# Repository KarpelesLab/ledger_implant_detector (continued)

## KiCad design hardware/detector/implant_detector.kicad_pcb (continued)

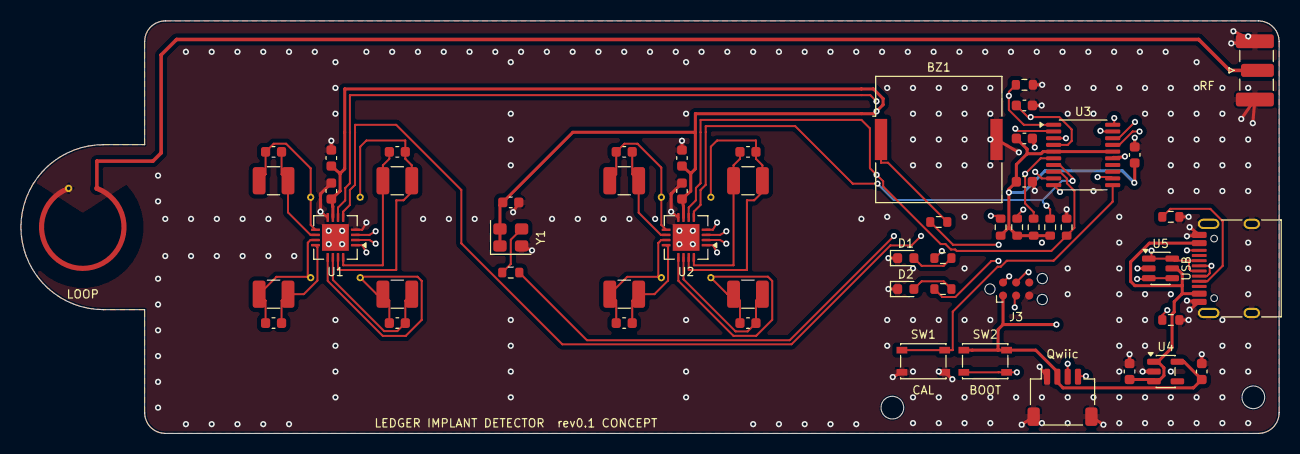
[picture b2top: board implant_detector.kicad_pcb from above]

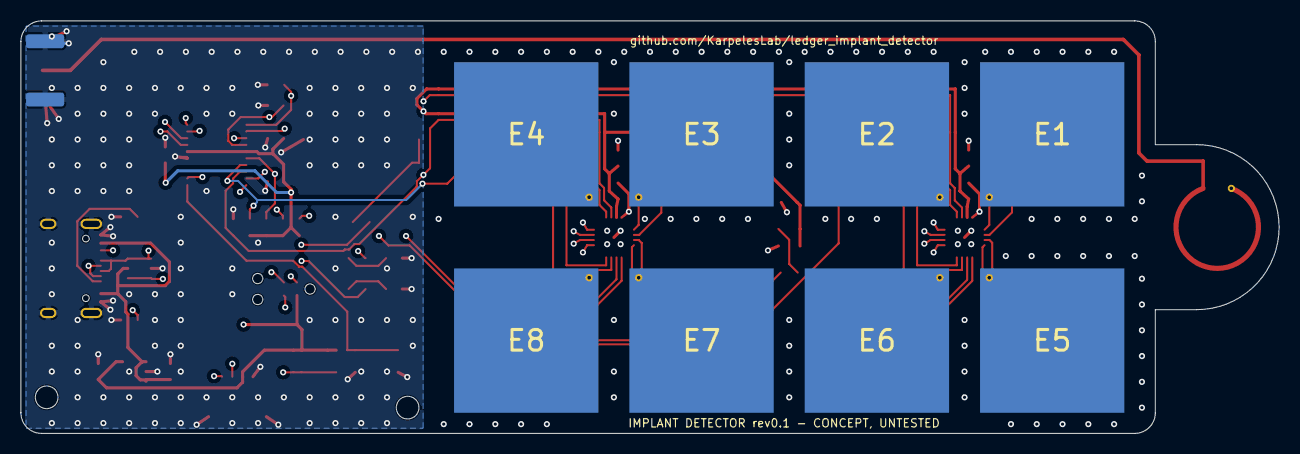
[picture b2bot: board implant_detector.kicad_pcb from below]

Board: 4 copper layers, 122.0 x 40.0 mm, 65 parts (8 on the bottom side), 42 nets.

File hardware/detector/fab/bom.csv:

"Designator","Value","Footprint","MPN","Manufacturer","LCSC","Qty","DNP"
"BZ1","PKLCS1212E4001","Buzzer_Beeper:Buzzer_Murata_PKLCS1212E","PKLCS1212E4001-R1","Murata","","1",""
"C1-C8","33p","Capacitor_SMD:C_0603_1608Metric","GRM1885C1H330FA01D","Murata","","8",""
"C9,C10,C13","4.7u","Capacitor_SMD:C_0603_1608Metric","","","","3",""
"C11,C12,C14,C15,C17,C19","100n","Capacitor_SMD:C_0603_1608Metric","","","","6",""
"C16,C18","1u","Capacitor_SMD:C_0603_1608Metric","","","","2",""
"D1","GREEN","LED_SMD:LED_0603_1608Metric","19-217/GHC-YR1S2/3T","Everlight","","1",""
"D2","RED","LED_SMD:LED_0603_1608Metric","19-217/R6C-AL1M2VY/3T","Everlight","","1",""
"J1","USB-C","Connector_USB:USB_C_Receptacle_HRO_TYPE-C-31-M-12","TYPE-C-31-M-12","Korean Hroparts Elec","C165948","1",""
"J2","Qwiic","Connector_JST:JST_SH_SM04B-SRSS-TB_1x04-1MP_P1.00mm_Horizontal","SM04B-SRSS-TB(LF)(SN)","JST","","1",""
"J4","SMA","Connector_Coaxial:SMA_Samtec_SMA-J-P-H-ST-EM1_EdgeMount","SMA-J-P-H-ST-EM1","Samtec","","1",""
"L1-L8","18u","Inductor_SMD:L_1210_3225Metric","CMH322522-180KL","Bourns","","8",""
"R1,R2","5.1k","Resistor_SMD:R_0603_1608Metric","","","","2",""
"R3,R9,R10","10k","Resistor_SMD:R_0603_1608Metric","","","","3",""
"R4,R5","1k","Resistor_SMD:R_0603_1608Metric","","","","2",""
"R6","100","Resistor_SMD:R_0603_1608Metric","","","","1",""
"R7,R8","4.7k","Resistor_SMD:R_0603_1608Metric","","","","2",""
"R11","100k","Resistor_SMD:R_0603_1608Metric","","","","1",""
"R12","33","Resistor_SMD:R_0603_1608Metric","","","","1",""
"SW1","CAL","Button_Switch_SMD:SW_SPST_PTS810","PTS810 SJM 250 SMTR LFS","C&K","","1",""
"SW2","BOOT","Button_Switch_SMD:SW_SPST_PTS810","PTS810 SJM 250 SMTR LFS","C&K","","1",""
"U1,U2","FDC2214","Package_DFN_QFN:WQFN-16-1EP_4x4mm_P0.5mm_EP2.6x2.6mm","FDC2214RGHR","Texas Instruments","","2",""
"U3","STM32F042F6P6","Package_SO:TSSOP-20_4.4x6.5mm_P0.65mm","STM32F042F6P6","STMicroelectronics","","1",""
"U4","AP2112K-3.3","Package_TO_SOT_SMD:SOT-23-5","AP2112K-3.3TRG1","Diodes Inc","","1",""
"U5","USBLC6-2SC6","Package_TO_SOT_SMD:SOT-23-6","USBLC6-2SC6","STMicroelectronics","","1",""
"Y1","40MHz","Oscillator:Oscillator_SMD_Abracon_ASE-4Pin_3.2x2.5mm","ASE-40.000MHZ-LC-T","Abracon","","1",""

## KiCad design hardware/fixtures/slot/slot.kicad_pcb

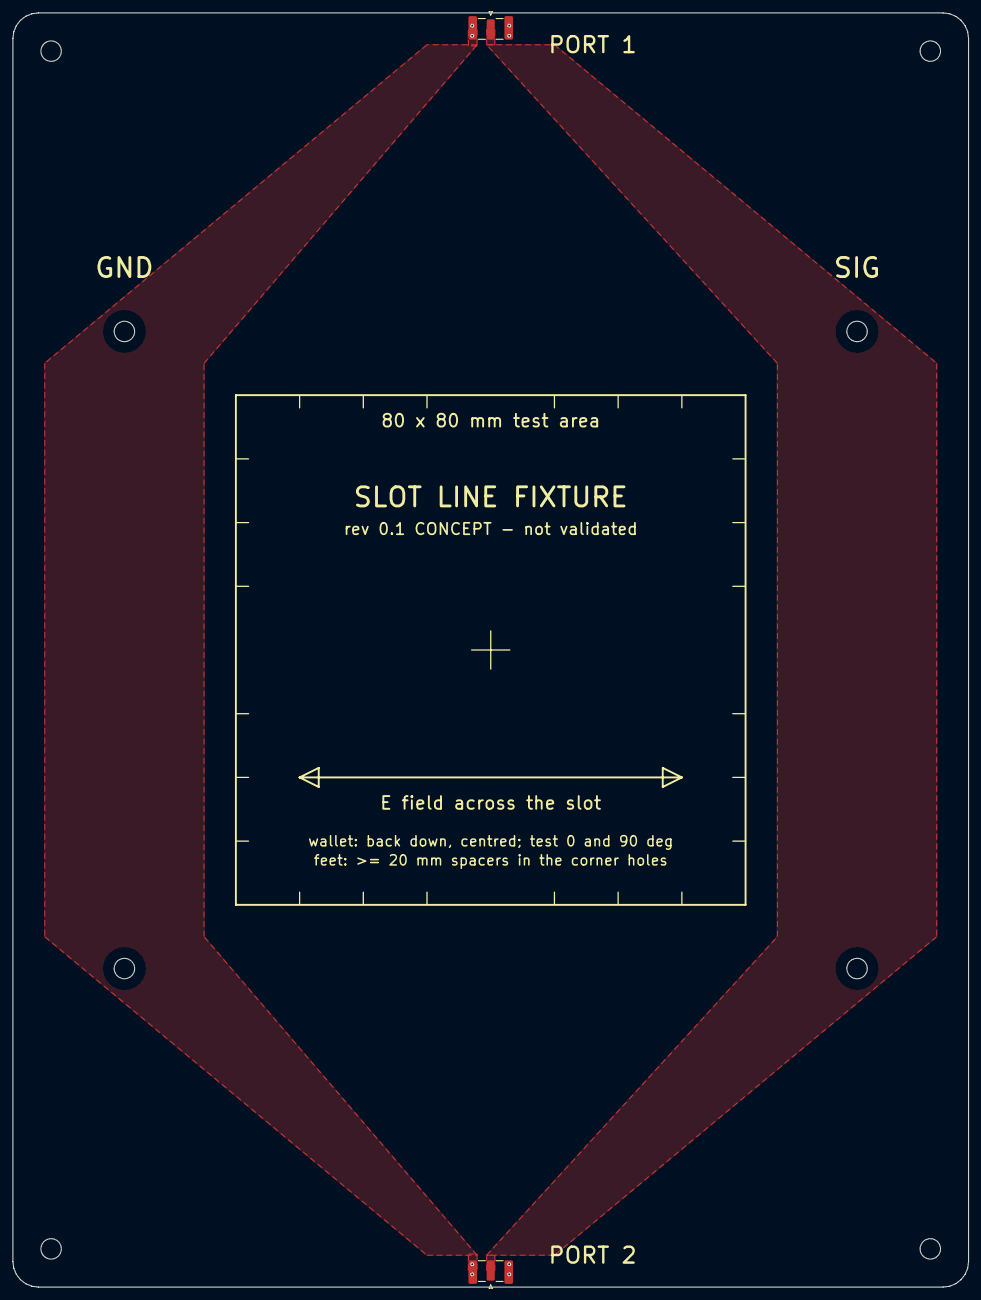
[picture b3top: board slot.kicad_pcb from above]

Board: 2 copper layers, 150.0 x 200.0 mm, 10 parts (0 on the bottom side), 2 nets, no tracks yet.

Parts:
H1, H2, H3, H4, H5, H6, H7, H8: MountingHole_3.2mm_M3
J1, J2: SMA edge jack (Samtec SMA-J-P-H-ST-EM1); SMA_Samtec_SMA-J-P-H-ST-EM1_EdgeMount

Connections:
GND: J1.2, J2.2
SIG: J1.1, J2.1

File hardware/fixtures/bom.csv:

Item,Qty per kit,Used on,Designators,Description,Suggested part,Notes
1,4,slot (2) + tem_base (2),J1 J2,"SMA female jack, edge mount / end launch, for 1.6 mm PCB, 50 ohm","Samtec SMA-J-P-H-ST-EM1 (footprint used); generic 'SMA-KE 1.6 mm' edge jacks also fit (e.g. Adafruit 1865)",Hand-soldered: centre pin + 2 legs top + 2 legs bottom
2,4,carrier,H1-H4,"M3 nylon hex spacer, female-female, 5 / 10 / 15 / 20 mm (one set of 4 per height you want to test)",any,Nylon only near the test area
3,4,tem_base + tem_plate,H1-H4,"M3 nylon hex spacer, female-female, 15 / 20 / 25 / 30 mm (one set of 4 per cell height h)",any,20 mm = 50 ohm cell
4,8,slot + tem_base,H5-H8,"M3 nylon spacer >= 20 mm, used as feet",any,
5,24,all,,M3 x 6 nylon screw,any,
6,1,tem_plate + 2 x tem_ramp,,"Conductive copper foil tape, 5-10 mm wide (conductive adhesive)",any,Ramp-to-septum joints; tack-solder
7,1,either fixture,,"SMA 50 ohm termination, male",any (the NanoVNA calibration load works),Only for S11-only tests

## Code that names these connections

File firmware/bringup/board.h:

// Rev 0.2 / 0.3 integrated board: Pico pin map, the same on both (tools/gen_integrated_sch.py, docs/rev02_integrated.md)
#pragma once

#define PIN_I2C_SDA     0   // ADS1115 at 0x48, 4.7k pull-ups
#define PIN_I2C_SCL     1
#define PIN_SYN_CLK     2   // ADF4351 3-wire bus (bit-banged)
#define PIN_SYN_DATA    3
#define PIN_ADC_RDY     4   // ADS1115 ALERT/RDY, 10k pull-up
#define PIN_SYN_LE      5
#define PIN_SYN_CE      6
#define PIN_SYN_PDBRF   7
#define PIN_SYN_LD      8   // lock detect pin
#define PIN_SYN_MUX     9   // MUXOUT, programmed as digital lock detect too
#define PIN_LCD_SCK     10  // SPI1
#define PIN_LCD_SDA     11
#define PIN_LCD_BL      12
#define PIN_LCD_CS      13
#define PIN_LCD_DC      14
#define PIN_LCD_RST     15
#define PIN_LED_G       16
#define PIN_LED_R       17
#define PIN_BTN         18  // to GND, internal pull-up

#define ADS1115_ADDR    0x48
#define ADC_CH_DET      0   // AD8318 VOUT through 1k / 10n
#define ADC_CH_DETTEMP  1   // AD8318 TEMP
#define ADC_CH_5VA      2   // +5VA / 2 (after FB1, not VBUS)
#define ADC_CH_SPARE    3   // J4 pin 10, TP6

#define SYN_REF_HZ      25000000u

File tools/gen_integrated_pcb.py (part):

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    router: they landed 9-35 mm away (C15 on VVCO 35 mm, C10 on TEMP 29 mm, a 43 mm VTUNE through
    TP2), and the router threaded other nets between their pads and along the RF lines.

    U2 right side, pins 17-24: VVCO runs out along one line, C16 (100p), C15 (100n) and FB2 hang
    off it into the band above the RFOUT turns. TEMP, RSET and VREF each have a part in the first
    column, VCOM passes between them to C11 in the second. VTUNE drops to In1 right at pin 20 and
    runs under the chip, between the exposed pad vias, to the loop filter on the left.
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        y = -Y1 + 5
        while y < Y1 - 3:
            inside = abs(x) < 9.5 and abs(y) > LAND0 - 8
            # off the pads: one on U3 pins 1-2 left them short of solder on the first JLC run
            if not inside and free.ok(x, y, 0.65, on_pads=False):
                bd.via(x, y, 'GND')
            y += 10.0
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    bd.text('Pico 2: micro-USB and BOOTSEL here', 100, 22.5, 1.4, pcbnew.B_SilkS, mirror=True)
    bd.text('SOURCE - fit shield can on this frame', 32, -71, 1.4, pcbnew.B_SilkS, mirror=True)
    bd.text('DETECTOR - fit shield can on this frame', 32, 71, 1.4, pcbnew.B_SilkS, mirror=True)
    bd.text('J4: spare GPIO / ADC / RUN', 86, 76, 1.4, pcbnew.B_SilkS, mirror=True)
    return bd


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
def rf_neighbours(bd, gap=1.0):
    """Router tracks on B.Cu running within `gap` mm of the hand-drawn RF lines (the 50 ohm chains and the
    U2/U3 RF pins): printed, so that a coupling path like rev 0.3's SYN_TEMP along RFOUTA+ shows up."""
    rf = [t for t in bd.b.GetTracks() if t.IsLocked() and t.Type() != pcbnew.PCB_VIA_T and t.GetLayer() == pcbnew.B_Cu
          and t.GetNetname().lstrip('/') in RF_NETS + ('RFA_P',)]
    near = {}
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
